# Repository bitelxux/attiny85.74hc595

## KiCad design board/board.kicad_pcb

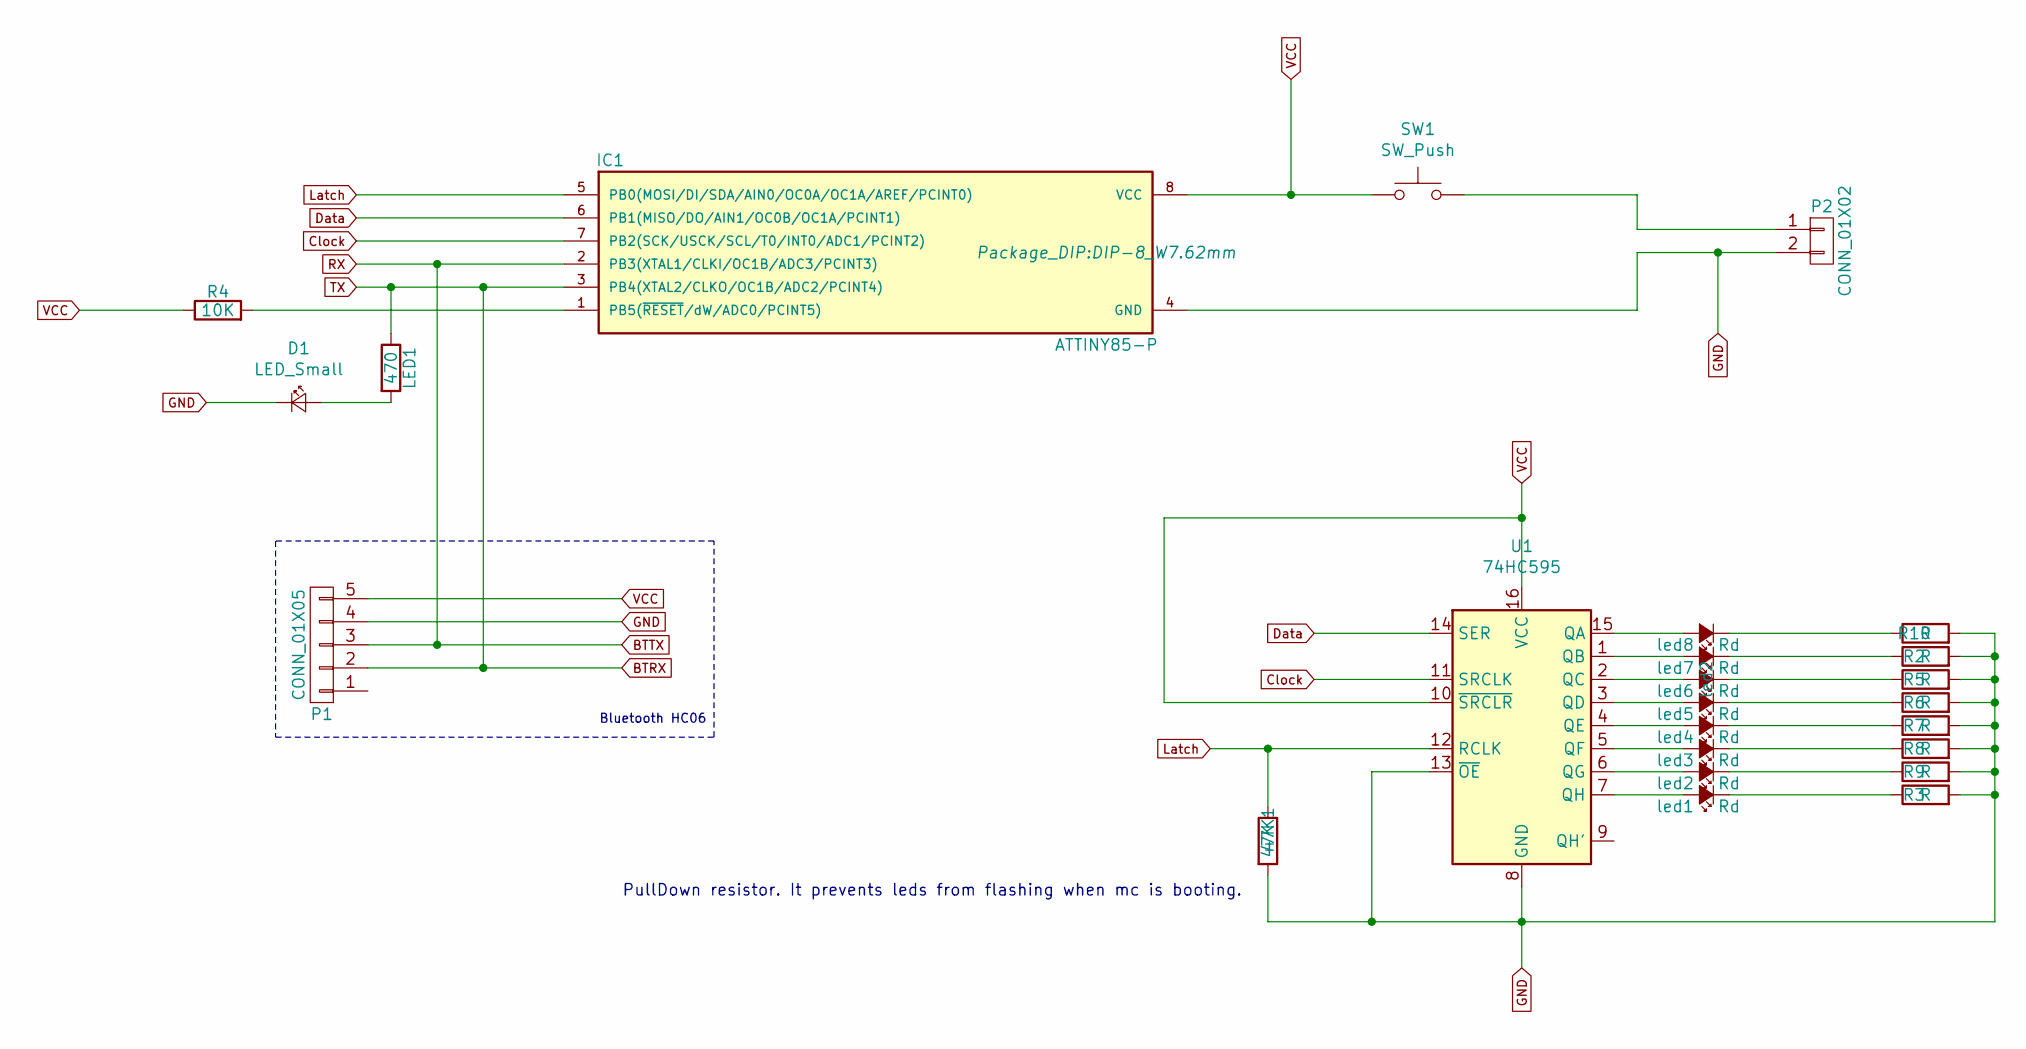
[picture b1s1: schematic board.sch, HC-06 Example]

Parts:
47K1: 47K; R_Axial_DIN0207_L6.3mm_D2.5mm_P7.62mm_Horizontal
D1: LED_Small; LED_D3.0mm
IC1: ATTINY85-P; DIP-8_W7.62mm
LED1: 470; R_Axial_DIN0207_L6.3mm_D2.5mm_P7.62mm_Horizontal
P1: CONN_01X05; Socket_Strip_Angled_1x05
P2: CONN_01X02; Pin_Header_Straight_1x02
R2, R3, R5, R6, R7, R8, R9, R10: R; R_Axial_DIN0207_L6.3mm_D2.5mm_P7.62mm_Horizontal
R4: 10K; R_Axial_DIN0207_L6.3mm_D2.5mm_P7.62mm_Horizontal
SW1: SW_Push; SW_PUSH_6mm_H4.3mm
U1: 74HC595; DIP-16_W7.62mm
led1, led2, led3, led4, led5, led6, led7, led8: Rd; LED_D3.0mm

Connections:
BTRX: IC1.3 (PB4(XTAL2/CLKO/OC1B/ADC2/PCINT4)), LED1.1, P1.2
BTTX: IC1.2 (PB3(XTAL1/CLKI/OC1B/ADC3/PCINT3)), P1.3
Clock: IC1.7 (PB2(SCK/USCK/SCL/T0/INT0/ADC1/PCINT2)), U1.11 (SRCLK)
Data: IC1.6 (PB1(MISO/DO/AIN1/OC0B/OC1A/PCINT1)), U1.14 (SER)
GND: 47K1.2, D1.1 (K), IC1.4 (GND), P1.4, P2.2, R2.2, R3.2, R5.2, R6.2, R7.2, R8.2, R9.2, R10.2, U1.8 (GND), U1.13 (~OE)
Latch: 47K1.1, IC1.5 (PB0(MOSI/DI/SDA/AIN0/OC0A/OC1A/AREF/PCI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), U1.12 (RCLK)
unnamed: D1.2 (A), LED1.2
unnamed: IC1.1 (PB5(~RESET~/dW/ADC0/PCINT5)), R4.2
unnamed: P2.1, SW1.2
unnamed: R2.1, led7.1 (K)
unnamed: R3.1, led1.1 (K)
unnamed: R5.1, led6.1 (K)
unnamed: R6.1, led5.1 (K)
unnamed: R7.1, led4.1 (K)
unnamed: R8.1, led3.1 (K)
unnamed: R9.1, led2.1 (K)
unnamed: R10.1, led8.1 (K)
unnamed: U1.1 (QB), led7.2 (A)
unnamed: U1.2 (QC), led6.2 (A)
unnamed: U1.3 (QD), led5.2 (A)
unnamed: U1.4 (QE), led4.2 (A)
unnamed: U1.5 (QF), led3.2 (A)
unnamed: U1.6 (QG), led2.2 (A)
unnamed: U1.7 (QH), led1.2 (A)
unnamed: U1.15 (QA), led8.2 (A)
VCC: IC1.8 (VCC), P1.5, R4.1, SW1.1, U1.10 (~SRCLR), U1.16 (VCC)

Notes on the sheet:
Bluetooth HC06
PullDown resistor. It prevents leds from flashing when mc is booting.

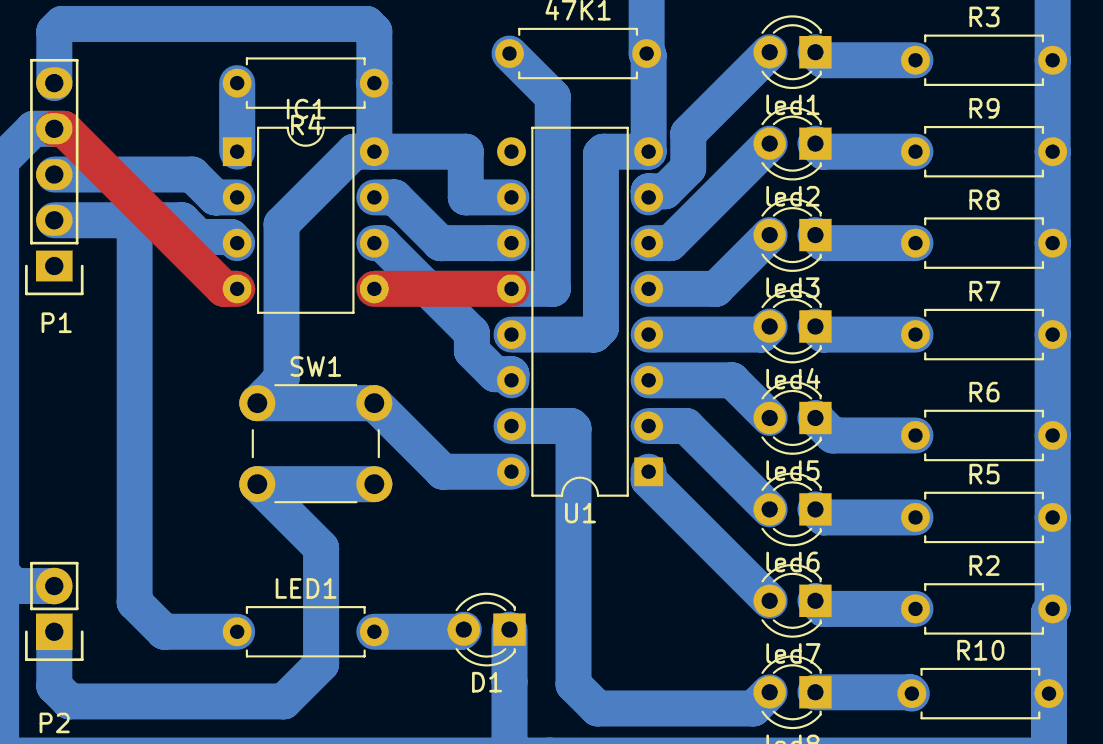
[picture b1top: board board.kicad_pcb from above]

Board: 2 copper layers, 25 parts (0 on the bottom side), 26 nets.

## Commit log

2019-02-26 exclude *-bak
2019-02-26 Not relevant for this project
2019-02-26 Leds and arrangement changed and high priority for speed change.
2019-03-04 hello and house keeping
2019-03-06 game4: Count in binary
2019-03-06 fast reaction on game change
